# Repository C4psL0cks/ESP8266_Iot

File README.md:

# [ESP8266](https://github.com/C4psL0cks/ESP8266)

## Download and Installation

To begin using this template, choose one of the following options to get started:

-   Install via npm: `npm i `
-   Clone the repo: `git clone https://github.com/C4psL0cks/ESP8266 `

## การใช้งานเริ่มต้นและการใช้งาน Application ต่างๆ

- แหล่งรวบรวม iot และเผยแพร่ สำหรับผู้สนใจนำไปต่อยอด โดยสามารถใช้ได้กับ ESP8266 และ ESP32    
- การใช้งาน LINE API 
- การใช่งาน SQL 
- การใช้งาน Firebase 
- การใช้งาน blynk
- การใช้งาน sensoer DHT22,BME820
- การใช้งาน ic ขยายขา digital

## วิธีสร้าง Line Token

- ทำการ Log in ที่ https://notify-bot.line.me/en/

- จากนั้น เข้าไปที่ https://notify-bot.line.me/my/  เพื่อทำการ สร้าง Line Token ขึ้นมา
- ให้กดปุ่ม **Generate token**

- ตั้งชื่อ Token อะไรก็ได้
- พร้อมทั้งเลือก กลุ่มใน Line ที่ต้องการให้มีการแจ้งเตือนไปยังกลุ่ม

## วิธีสร้าง Wifi manager ร่วมกับ blynk

- เข้าไปใน Exsample wifi manager 
- ให้เพิ่มคำสั่ง blynk.config(token); เข้าไป ก็จะสามารถเชื่อมต่อกับ blynk ได้

## Version

# Reference

ESP8266 Documents
- <https://arduino-esp8266.readthedocs.io/en/latest/index.html>

ESP8266
- <https://github.com/esp8266>

Firebase
- <https://firebase-arduino.readthedocs.io/en/latest/>

PHP
- <https://www.praphas.com/forum/index.php?PHPSESSID=7b9fa1rmfb5eit80kmtkkto662&topic=327.0>

PHP
- <https://www.praphas.com/forum/index.php?board=27.0>

LINE Notify

- <https://notify-bot.line.me/th/>

LINE richmenumaker

- <https://lineforbusiness.com/richmenumaker/>

LINE developers

- <https://developers.line.biz/en/>

Name API.com 
-   <https://www.name.com/api-docs/>

MongoDB
-   <http://mongodb.github.io>

Node.js MongoDB Driver API
-   <http://mongodb.github.io/node-mongodb-native/3.0/api/>

Express
-   <https://expressjs.com/en/starter/hello-world.html>

Node Js
-   <https://nodejs.org/api/synopsis.html>

Socket.io
-   <https://socket.io/get-started/chat/>

javascript.info
-   <https://javascript.info/?fbclid=IwAR195YbvLlcZEbOXenGaOHmnOuxKuDD_N2JJAbFTmWnEmwFSVzyRiaMRT0c>

## Copyright and License

Copyright 2013-2019 Blackrock Digital LLC. Code released under the [MIT](https://github.com/BlackrockDigital/startbootstrap-resume/blob/gh-pages/LICENSE) license.

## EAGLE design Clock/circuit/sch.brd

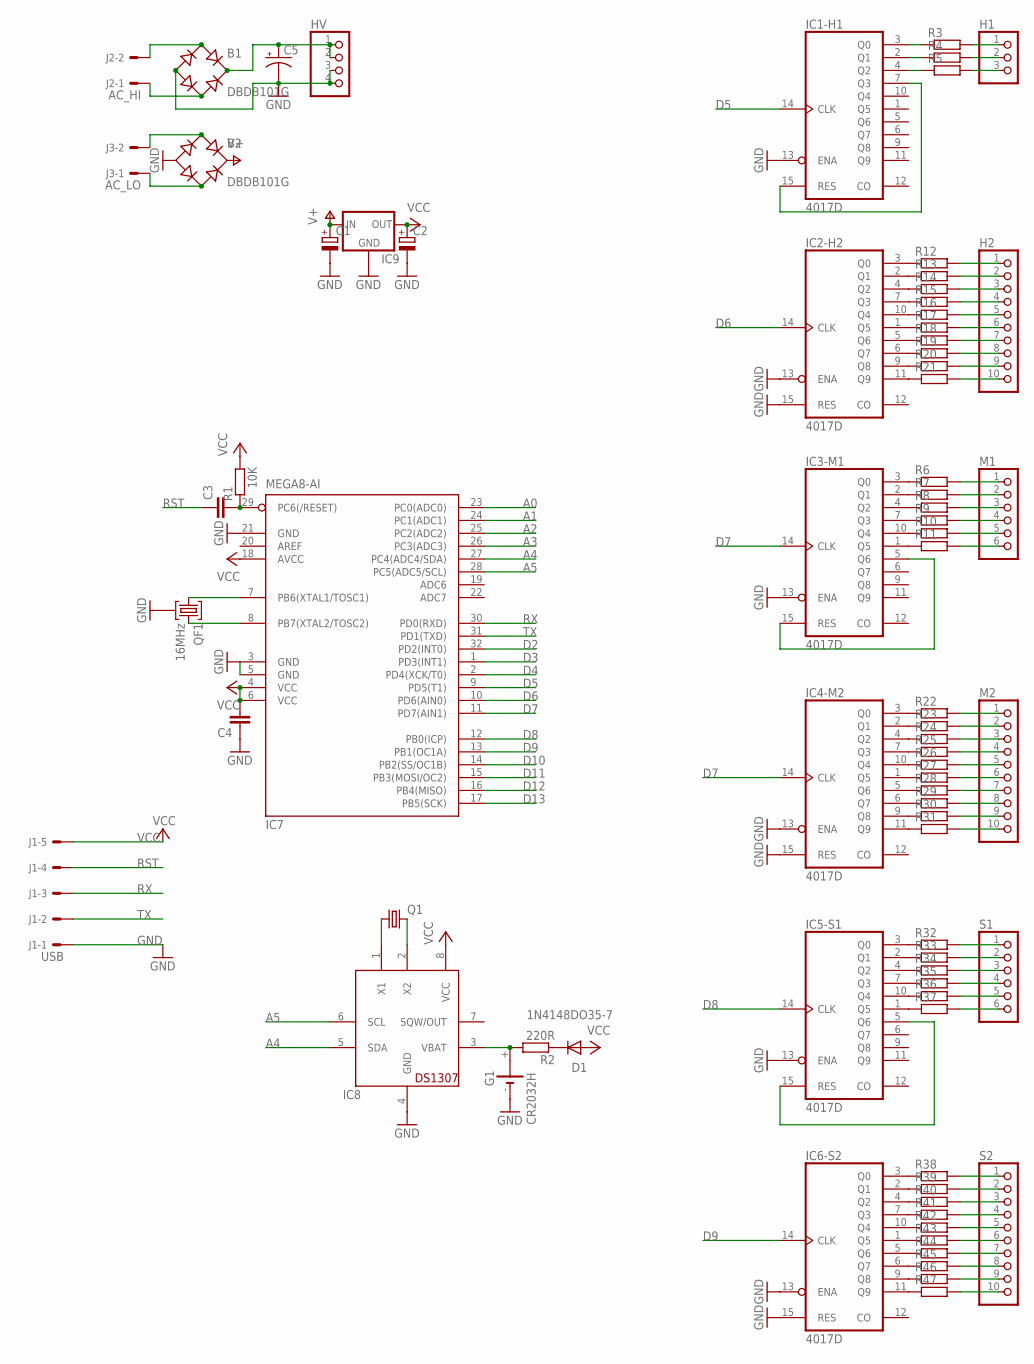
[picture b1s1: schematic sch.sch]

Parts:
B1, B2: DBDB101G; DB
C1, C2: CPOL-EU140CLH-1010; 140CLH-1010
C3, C4: C-EUC1206K; C1206K
C5: CPOL-USE5-13; E5-13
D1: 1N4148DO35-7; DO35-7
G1: CR2032H
H1: PINHD-1X3; 1X03
H2: PINHD-1X10; 1X10
HV: PINHD-1X4; 1X04
IC1-H1, IC2-H2, IC3-M1, IC4-M2, IC5-S1, IC6-S2: 4017D; SO16
IC7: MEGA8-AI; TQFP32-08
IC8: DS1307; DIL08
IC9: 78XXS
J1: USB; 7395-05
J2: AC_HI; 7395-02
J3: AC_LO; 7395-02
M1: PINHD-1X6; 1X06
M2: PINHD-1X10; 1X10
Q1: CRYSTALTC26H; TC26H
QF1: 16MHz; HC49U
R1: 10K; 0207/7
R2: 220R; 0207/7
R3, R4, R5, R6, R7, R8, R9, R10, R11, R12, R13, R14, R15, R16, R17, R18, R19, R20, R21, R22, R23, R24, R25, R26, R27, R28, R29, R30, R31, R32, R33, R34, R35, R36, R37, R38, R39, R40, R41, R42, R43, R44, R45, R46, R47: R-EU_0204/5; 0204/5
S1: PINHD-1X6; 1X06
S2: PINHD-1X10; 1X10

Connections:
A0: IC7.23 (PC0(ADC0))
A1: IC7.24 (PC1(ADC1))
A2: IC7.25 (PC2(ADC2))
A3: IC7.26 (PC3(ADC3))
A4: IC7.27 (PC4(ADC4/SDA)), IC8.5 (SDA)
A5: IC7.28 (PC5(ADC5/SCL)), IC8.6 (SCL)
D2: IC7.32 (PD2(INT0))
D3: IC7.1 (PD3(INT1))
D4: IC7.2 (PD4(XCK/T0))
D5: IC1-H1.14 (CLK), IC7.9 (PD5(T1))
D6: IC2-H2.14 (CLK), IC7.10 (PD6(AIN0))
D7: IC3-M1.14 (CLK), IC4-M2.14 (CLK), IC7.11 (PD7(AIN1))
D8: IC5-S1.14 (CLK), IC7.12 (PB0(ICP))
D9: IC6-S2.14 (CLK), IC7.13 (PB1(OC1A))
D10: IC7.14 (PB2(SS/OC1B))
D11: IC7.15 (PB3(MOSI/OC2))
D12: IC7.16 (PB4(MISO))
D13: IC7.17 (PB5(SCK))
GND: B1.-, B2.-, C1.-, C2.-, C4.1, C5.-, G1.-, HV.3, HV.4, IC1-H1.13 (ENA), IC2-H2.13 (ENA), IC2-H2.15 (RES), IC3-M1.13 (ENA), IC4-M2.13 (ENA), IC4-M2.15 (RES), IC5-S1.13 (ENA), IC6-S2.13 (ENA), IC6-S2.15 (RES), IC7.3 (GND), IC7.5 (GND), IC7.21 (GND), IC8.4 (GND), IC9.GND, J1.1, QF1.2
unnamed: IC1-H1.3 (Q0), R3.1
unnamed: IC1-H1.2 (Q1), R4.1
unnamed: IC1-H1.7 (Q3), IC1-H1.15 (RES)
unnamed: IC3-M1.3 (Q0), R6.1
unnamed: IC3-M1.2 (Q1), R7.1
unnamed: IC3-M1.4 (Q2), R8.1
unnamed: IC3-M1.7 (Q3), R9.1
unnamed: IC3-M1.10 (Q4), R10.1
unnamed: IC3-M1.1 (Q5), R11.1
unnamed: IC2-H2.3 (Q0), R12.1
unnamed: IC2-H2.2 (Q1), R13.1
unnamed: IC2-H2.4 (Q2), R14.1
unnamed: IC2-H2.7 (Q3), R15.1
unnamed: IC4-M2.3 (Q0), R22.1
unnamed: IC4-M2.2 (Q1), R23.1
unnamed: IC4-M2.4 (Q2), R24.1
unnamed: IC4-M2.7 (Q3), R25.1
unnamed: IC4-M2.10 (Q4), R26.1
unnamed: IC4-M2.1 (Q5), R27.1
unnamed: IC4-M2.5 (Q6), R28.1
unnamed: IC4-M2.6 (Q7), R29.1
unnamed: IC4-M2.9 (Q8), R30.1
unnamed: IC4-M2.11 (Q9), R31.1
unnamed: IC5-S1.3 (Q0), R32.1
unnamed: IC5-S1.2 (Q1), R33.1
unnamed: IC5-S1.4 (Q2), R34.1
unnamed: IC5-S1.7 (Q3), R35.1
unnamed: IC5-S1.10 (Q4), R36.1
unnamed: IC5-S1.5 (Q6), IC5-S1.15 (RES)
unnamed: IC5-S1.1 (Q5), R37.1
unnamed: IC6-S2.3 (Q0), R38.1
unnamed: IC6-S2.2 (Q1), R39.1
unnamed: IC6-S2.4 (Q2), R40.1
unnamed: IC6-S2.7 (Q3), R41.1
unnamed: IC6-S2.10 (Q4), R42.1
unnamed: IC6-S2.1 (Q5), R43.1
unnamed: IC6-S2.5 (Q6), R44.1
unnamed: IC6-S2.6 (Q7), R45.1
unnamed: IC6-S2.9 (Q8), R46.1
unnamed: IC2-H2.10 (Q4), R16.1
unnamed: IC2-H2.1 (Q5), R17.1
unnamed: IC2-H2.5 (Q6), R18.1
unnamed: IC2-H2.6 (Q7), R19.1
unnamed: IC2-H2.9 (Q8), R20.1
unnamed: IC2-H2.11 (Q9), R21.1
unnamed: IC3-M1.5 (Q6), IC3-M1.15 (RES)
unnamed: C3.2, IC7.29 (PC6(/RESET)), R1.1
unnamed: D1.C, R2.1
unnamed: B2.AC1, J3.2
unnamed: B2.AC2, J3.1
unnamed: IC7.7 (PB6(XTAL1/TOSC1)), QF1.1
unnamed: IC7.8 (PB7(XTAL2/TOSC2)), QF1.3
unnamed: IC8.1 (X1), Q1.1
unnamed: IC8.2 (X2), Q1.2
unnamed: G1.+, IC8.3 (VBAT), R2.2
unnamed: B1.AC2, J2.1
unnamed: B1.AC1, J2.2
unnamed: B1.+, C5.+, HV.1, HV.2
unnamed: H1.1, R3.2
unnamed: H1.2, R4.2
unnamed: H1.3, R5.2
unnamed: IC1-H1.4 (Q2), R5.1
unnamed: IC6-S2.11 (Q9), R47.1
unnamed: R47.2, S2.10
unnamed: R46.2, S2.9
unnamed: R45.2, S2.8
unnamed: R44.2, S2.7
unnamed: R43.2, S2.6
unnamed: R42.2, S2.5
unnamed: R41.2, S2.4
unnamed: R40.2, S2.3
unnamed: R39.2, S2.2
unnamed: R38.2, S2.1
unnamed: R32.2, S1.1
unnamed: R33.2, S1.2
unnamed: R34.2, S1.3
unnamed: R35.2, S1.4
unnamed: R36.2, S1.5
unnamed: R37.2, S1.6
unnamed: M2.10, R31.2
unnamed: M2.9, R30.2
unnamed: M2.8, R29.2
unnamed: M2.7, R28.2
unnamed: M2.6, R27.2
unnamed: M2.5, R26.2
unnamed: M2.4, R25.2
unnamed: M2.3, R24.2
unnamed: M2.2, R23.2
unnamed: M2.1, R22.2
unnamed: M1.6, R11.2
unnamed: M1.5, R10.2
unnamed: M1.4, R9.2
unnamed: M1.3, R8.2
unnamed: M1.2, R7.2
unnamed: M1.1, R6.2
unnamed: H2.10, R21.2
unnamed: H2.9, R20.2
unnamed: H2.8, R19.2
unnamed: H2.7, R18.2
unnamed: H2.6, R17.2
unnamed: H2.5, R16.2
unnamed: H2.4, R15.2
unnamed: H2.1, R12.2
unnamed: H2.2, R13.2
unnamed: H2.3, R14.2
RST: C3.1, J1.4
RX: IC7.30 (PD0(RXD)), J1.3
TX: IC7.31 (PD1(TXD)), J1.2
V+: B2.+, C1.+, IC9.IN
VCC: C2.+, C4.2, D1.A, IC7.4 (VCC), IC7.6 (VCC), IC7.18 (AVCC), IC8.8 (VCC), IC9.OUT, J1.5, R1.2
VDD: IC1-H1.16 (VDD), IC2-H2.16 (VDD), IC3-M1.16 (VDD), IC4-M2.16 (VDD), IC5-S1.16 (VDD), IC6-S2.16 (VDD)
VSS: IC1-H1.8 (VSS), IC2-H2.8 (VSS), IC3-M1.8 (VSS), IC4-M2.8 (VSS), IC5-S1.8 (VSS), IC6-S2.8 (VSS)

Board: 2 copper layers, 77 parts (0 on the bottom side), 120 nets, no tracks yet.

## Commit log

2018-06-21 Rename timezone.ino to Timezone.ino
2018-06-21 Rename wificonnectV1.ino to WificonnectV1.ino
2018-06-21 Rename anto.ino to Anto.ino
2018-06-21 Rename HTTP_GET_Requests.ino to HTTPS_GET_Requests.ino
2018-07-03 mach
2018-08-15 Rename ESp8266_Anto.ino to ESP8266_Anto.ino
2019-08-01 update nano
2019-08-29 update socket.io by mz
2019-09-13 update by mz
2019-10-03 update by maker
2019-12-25 by dev codings
2020-09-14 add License
2020-09-24 edit file
2020-10-11 new rgb
2021-04-24 fix renew name file
2021-06-02 update bug

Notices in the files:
README.md:
License: MIT
